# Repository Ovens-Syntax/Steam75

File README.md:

# Steam75
 a keyboard pcb by me with a slightly tweaked 75% layout (sorry im too lazy to integrate mcu so matrix pcb connects to dauter/dev board)

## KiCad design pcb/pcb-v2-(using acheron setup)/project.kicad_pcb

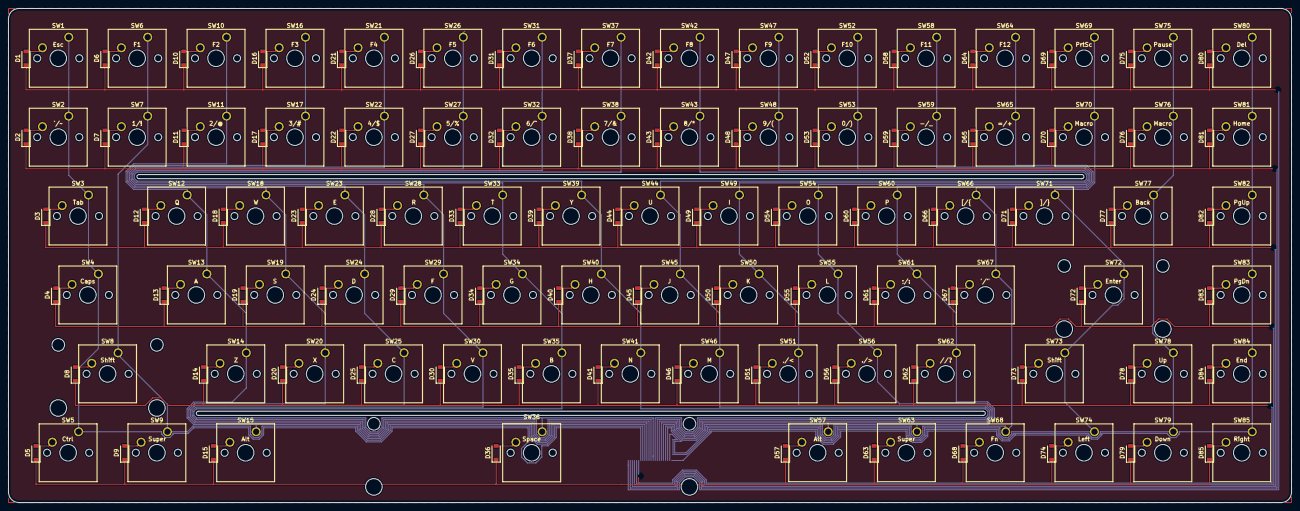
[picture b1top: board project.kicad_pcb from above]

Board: 2 copper layers, 309.8 x 119.3 mm, 171 parts (1 on the bottom side), 107 nets.

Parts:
D1, D2, D3, D4, D5, D6, D7, D8, D9, D10, D11, D12, D13, D14, D15, D16, D17, D18, D19, D20, D21, D22, D23, D24, D25, D26, D27, D28, D29, D30, D31, D32, D33, D34, D35, D36, D37, D38, D39, D40, D41, D42, D43, D44, D45, D46, D47, D48, D49, D50, D51, D52, D53, D54, D55, D56, D57, D58, D59, D60, D61, D62, D63, D64, D65, D66, D67, D68, D69, D70, D71, D72, D73, D74, D75, D76, D77, D78, D79, D80, D81, D82, D83, D84, D85: D_Small; D_SOD-123
J1: Conn_01x22_Female; Hirose_FH12-22S-0.5SH_1x22-1MP_P0.50mm_Horizontal
SW1, SW2, SW6, SW7, SW9, SW10, SW11, SW12, SW13, SW14, SW16, SW17, SW18, SW19, SW20, SW21, SW22, SW23, SW24, SW25, SW26, SW27, SW28, SW29, SW30, SW31, SW32, SW33, SW34, SW35, SW37, SW38, SW39, SW40, SW41, SW42, SW43, SW44, SW45, SW46, SW47, SW48, SW49, SW50, SW51, SW52, SW53, SW54, SW55, SW56, SW58, SW59, SW60, SW61, SW62, SW63, SW64, SW65, SW66, SW67, SW69, SW70, SW71, SW74, SW75, SW76, SW78, SW79, SW80, SW81, SW82, SW83, SW84, SW85: CherryMX; SW_Cherry_MX_1.00u_PCB
SW3, SW77: CherryMX; SW_Cherry_MX_1.50u_PCB
SW4, SW73: CherryMX; SW_Cherry_MX_1.75u_PCB
SW5, SW15, SW57, SW68: CherryMX; SW_Cherry_MX_1.25u_PCB
SW8, SW72: CherryMX; SW_Cherry_MX_2.25u_PCB
SW36: CherryMX; CherryMX_6.00u_PCB_StabWireBottom

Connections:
C1: J1.7, SW1.1, SW2.1, SW3.1, SW4.1, SW5.1
C2: J1.8, SW6.1, SW7.1, SW8.1, SW9.1
C3: J1.9, SW10.1, SW11.1, SW12.1, SW13.1, SW14.1, SW15.1
C4: J1.10, SW16.1, SW17.1, SW18.1, SW19.1, SW20.1
C5: J1.11, SW21.1, SW22.1, SW23.1, SW24.1, SW25.1
C6: J1.12, SW26.1, SW27.1, SW28.1, SW29.1, SW30.1
C7: J1.13, SW31.1, SW32.1, SW33.1, SW34.1, SW35.1, SW36.1
C8: J1.14, SW37.1, SW38.1, SW39.1, SW40.1, SW41.1
C9: J1.15, SW42.1, SW43.1, SW44.1, SW45.1, SW46.1
C10: J1.16, SW47.1, SW48.1, SW49.1, SW50.1, SW51.1
C11: J1.17, SW52.1, SW53.1, SW54.1, SW55.1, SW56.1, SW57.1
C12: J1.18, SW58.1, SW59.1, SW60.1, SW61.1, SW62.1, SW63.1
C13: J1.19, SW64.1, SW65.1, SW66.1, SW67.1, SW68.1
C14: J1.20, SW69.1, SW70.1, SW71.1, SW72.1, SW73.1, SW74.1
C15: J1.21, SW75.1, SW76.1, SW77.1, SW78.1, SW79.1
C16: J1.22, SW80.1, SW81.1, SW82.1, SW83.1, SW84.1, SW85.1
unnamed: D1.2 (A), SW1.2
unnamed: D2.2 (A), SW2.2
unnamed: D3.2 (A), SW3.2
unnamed: D6.2 (A), SW6.2
unnamed: D8.2 (A), SW8.2
unnamed: D9.2 (A), SW9.2
unnamed: D10.2 (A), SW10.2
unnamed: D12.2 (A), SW12.2
unnamed: D14.2 (A), SW14.2
unnamed: D16.2 (A), SW16.2
unnamed: D18.2 (A), SW18.2
unnamed: D19.2 (A), SW19.2
unnamed: D20.2 (A), SW20.2
unnamed: D21.2 (A), SW21.2
unnamed: D23.2 (A), SW23.2
unnamed: D26.2 (A), SW26.2
unnamed: D28.2 (A), SW28.2
unnamed: D29.2 (A), SW29.2
unnamed: D30.2 (A), SW30.2
unnamed: D31.2 (A), SW31.2
unnamed: D33.2 (A), SW33.2
unnamed: D34.2 (A), SW34.2
unnamed: D36.2 (A), SW36.2
unnamed: D37.2 (A), SW37.2
unnamed: D39.2 (A), SW39.2
unnamed: D40.2 (A), SW40.2
unnamed: D41.2 (A), SW41.2
unnamed: D42.2 (A), SW42.2
unnamed: D44.2 (A), SW44.2
unnamed: D45.2 (A), SW45.2
unnamed: D46.2 (A), SW46.2
unnamed: D47.2 (A), SW47.2
unnamed: D49.2 (A), SW49.2
unnamed: D50.2 (A), SW50.2
unnamed: D52.2 (A), SW52.2
unnamed: D54.2 (A), SW54.2
unnamed: D55.2 (A), SW55.2
unnamed: D57.2 (A), SW57.2
unnamed: D58.2 (A), SW58.2
unnamed: D60.2 (A), SW60.2
unnamed: D63.2 (A), SW63.2
unnamed: D64.2 (A), SW64.2
unnamed: D66.2 (A), SW66.2
unnamed: D68.2 (A), SW68.2
unnamed: D69.2 (A), SW69.2
unnamed: D70.2 (A), SW70.2
unnamed: D71.2 (A), SW71.2
unnamed: D72.2 (A), SW72.2
unnamed: D73.2 (A), SW73.2
unnamed: D74.2 (A), SW74.2
unnamed: D75.2 (A), SW75.2
unnamed: D76.2 (A), SW76.2
unnamed: D78.2 (A), SW78.2
unnamed: D79.2 (A), SW79.2
unnamed: D80.2 (A), SW80.2
unnamed: D81.2 (A), SW81.2
unnamed: D82.2 (A), SW82.2
unnamed: D83.2 (A), SW83.2
unnamed: D84.2 (A), SW84.2
unnamed: D85.2 (A), SW85.2
unnamed: D4.2 (A), SW4.2
unnamed: D5.2 (A), SW5.2
unnamed: D7.2 (A), SW7.2
unnamed: D11.2 (A), SW11.2
unnamed: D13.2 (A), SW13.2
unnamed: D15.2 (A), SW15.2
unnamed: D17.2 (A), SW17.2
unnamed: D22.2 (A), SW22.2
unnamed: D24.2 (A), SW24.2
unnamed: D25.2 (A), SW25.2
unnamed: D27.2 (A), SW27.2
unnamed: D32.2 (A), SW32.2
unnamed: D35.2 (A), SW35.2
unnamed: D38.2 (A), SW38.2
unnamed: D43.2 (A), SW43.2
unnamed: D48.2 (A), SW48.2
unnamed: D51.2 (A), SW51.2
unnamed: D53.2 (A), SW53.2
unnamed: D56.2 (A), SW56.2
unnamed: D59.2 (A), SW59.2
unnamed: D61.2 (A), SW61.2
unnamed: D62.2 (A), SW62.2
unnamed: D65.2 (A), SW65.2
unnamed: D67.2 (A), SW67.2
unnamed: D77.2 (A), SW77.2
R1: D1.1 (K), D6.1 (K), D10.1 (K), D16.1 (K), D21.1 (K), D26.1 (K), D31.1 (K), D37.1 (K), D42.1 (K), D47.1 (K), D52.1 (K), D58.1 (K), D64.1 (K), D69.1 (K), D75.1 (K), D80.1 (K), J1.1
R2: D2.1 (K), D7.1 (K), D11.1 (K), D17.1 (K), D22.1 (K), D27.1 (K), D32.1 (K), D38.1 (K), D43.1 (K), D48.1 (K), D53.1 (K), D59.1 (K), D65.1 (K), D70.1 (K), D76.1 (K), D81.1 (K), J1.2
R3: D3.1 (K), D12.1 (K), D18.1 (K), D23.1 (K), D28.1 (K), D33.1 (K), D39.1 (K), D44.1 (K), D49.1 (K), D54.1 (K), D60.1 (K), D66.1 (K), D71.1 (K), D77.1 (K), D82.1 (K), J1.3
R4: D4.1 (K), D13.1 (K), D19.1 (K), D24.1 (K), D29.1 (K), D34.1 (K), D40.1 (K), D45.1 (K), D50.1 (K), D55.1 (K), D61.1 (K), D67.1 (K), D72.1 (K), D83.1 (K), J1.4
R5: D8.1 (K), D14.1 (K), D20.1 (K), D25.1 (K), D30.1 (K), D35.1 (K), D41.1 (K), D46.1 (K), D51.1 (K), D56.1 (K), D62.1 (K), D73.1 (K), D78.1 (K), D84.1 (K), J1.5
R6: D5.1 (K), D9.1 (K), D15.1 (K), D36.1 (K), D57.1 (K), D63.1 (K), D68.1 (K), D74.1 (K), D79.1 (K), D85.1 (K), J1.6

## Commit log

2023-01-09 Create pcb
2023-01-09 add files
2023-01-12 add mooore file
2023-01-12 add version using acheron setup
2023-01-16 added stuff
    ik I am bad at commits so what whos gonna stop me *evil laughing*
2023-02-01 wiring added
2023-02-07 route but ima have to do a fucking nother gen of iterating ahahh
2023-02-08 routing v1 done and space bar stab added
2023-02-08 saved all stuff
2023-03-22 draft routing complete now i refine
2023-03-22 draft routing complete now refining ig
2023-03-22 trying to degoof the project
2023-03-22 Revert "saved all stuff"
    This reverts commit 74072fa5d8b5083dce3dbcdb3dc12365b1835386.
2023-03-26 draft done? needs review
2023-03-28 doneish?
2023-05-21 push so i can work on my laptop
2023-05-21 Create build-notes
